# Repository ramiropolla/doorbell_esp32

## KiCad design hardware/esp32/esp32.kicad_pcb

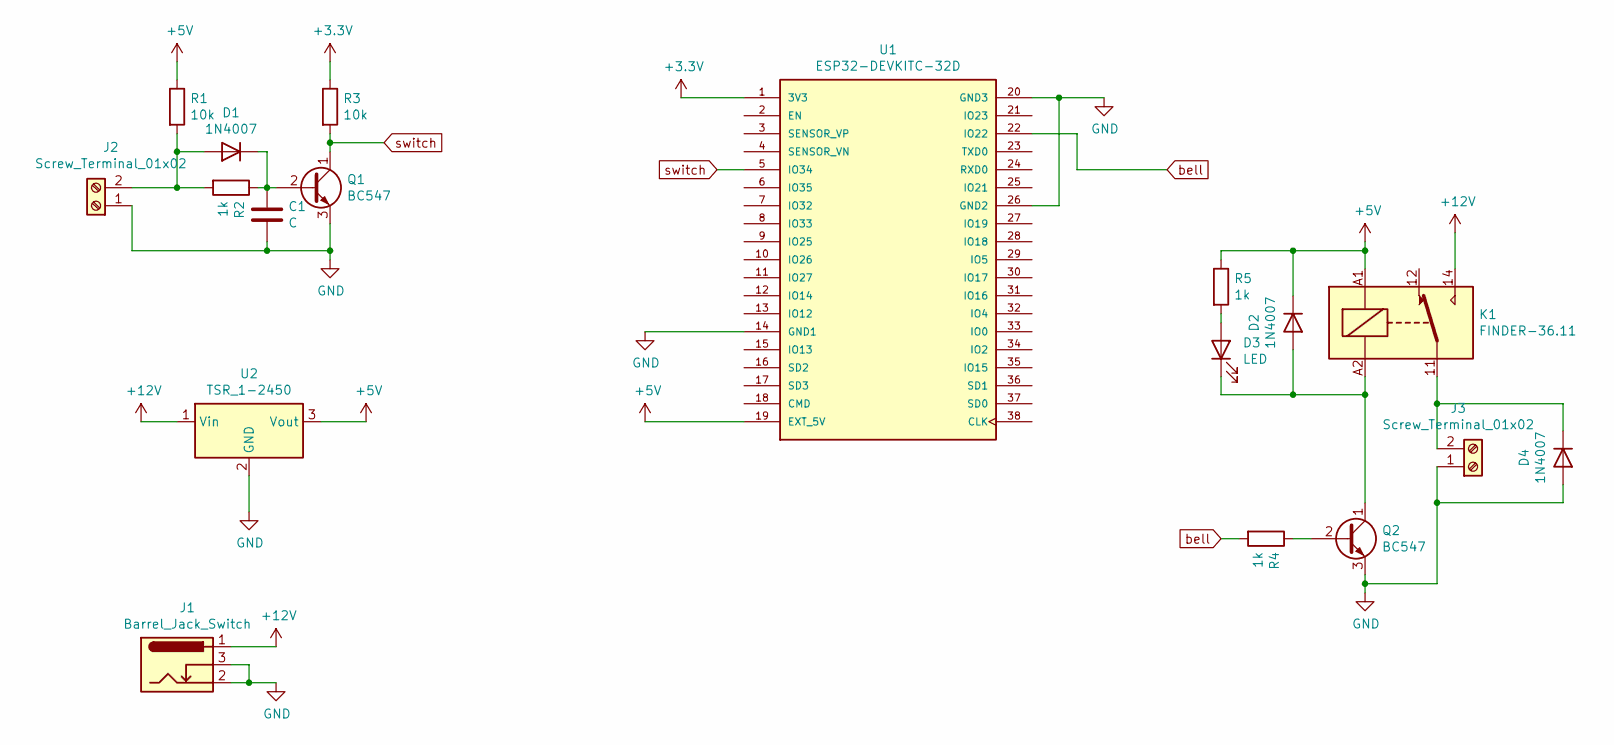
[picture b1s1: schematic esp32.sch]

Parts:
C1: C; C_Disc_D3.0mm_W1.6mm_P2.50mm
D1, D2, D4: 1N4007; D_DO-41_SOD81_P7.62mm_Horizontal
D3: LED; LED_D10.0mm
J1: Barrel_Jack_Switch; BarrelJack_Horizontal
J2, J3: Screw_Terminal_01x02; TerminalBlock_bornier-2_P5.08mm
K1: FINDER-36.11; Relay_SPDT_Finder_36.11
Q1, Q2: BC547; TO-92
R1, R3: 10k; R_Axial_DIN0207_L6.3mm_D2.5mm_P7.62mm_Horizontal
R2, R4, R5: 1k; R_Axial_DIN0207_L6.3mm_D2.5mm_P7.62mm_Horizontal
U1: ESP32-DEVKITC-32D; MODULE_ESP32-DEVKITC-32D; PARTREV 4
U2: TSR_1-2450; Converter_DCDC_TRACO_TSR-1_THT

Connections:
+3V3: R3.1, U1.1 (3V3)
+5V: D2.1 (K), K1.A1, R1.1, R5.1, U1.19 (EXT_5V), U2.3 (Vout)
+12V: J1.1, K1.14, U2.1 (Vin)
GND: C1.2, D4.2 (A), J1.2, J1.3, J2.1, J3.1, Q1.3 (E), Q2.3 (E), U1.14 (GND1), U1.20 (GND3), U1.26 (GND2), U2.2 (GND)
unnamed: C1.1, D1.1 (K), Q1.2 (B), R2.1
unnamed: D1.2 (A), J2.2, R1.2, R2.2
unnamed: D2.2 (A), D3.1 (K), K1.A2, Q2.1 (C)
unnamed: D3.2 (A), R5.2
unnamed: D4.1 (K), J3.2, K1.11
unnamed: Q2.2 (B), R4.1
bell: R4.2, U1.22 (IO22)
switch: Q1.1 (C), R3.2, U1.5 (IO34)

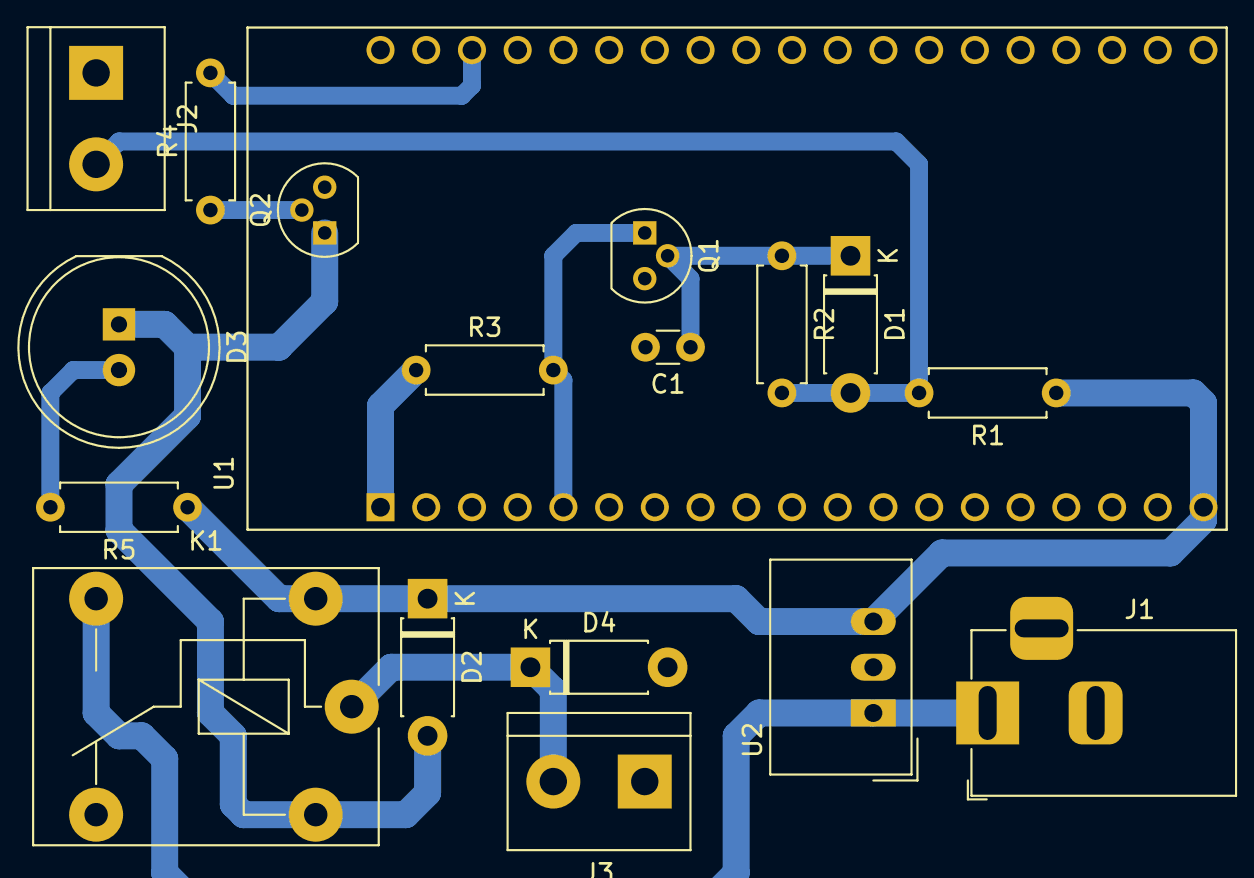
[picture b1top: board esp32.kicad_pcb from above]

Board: 2 copper layers, 18 parts (0 on the bottom side), 12 nets.
